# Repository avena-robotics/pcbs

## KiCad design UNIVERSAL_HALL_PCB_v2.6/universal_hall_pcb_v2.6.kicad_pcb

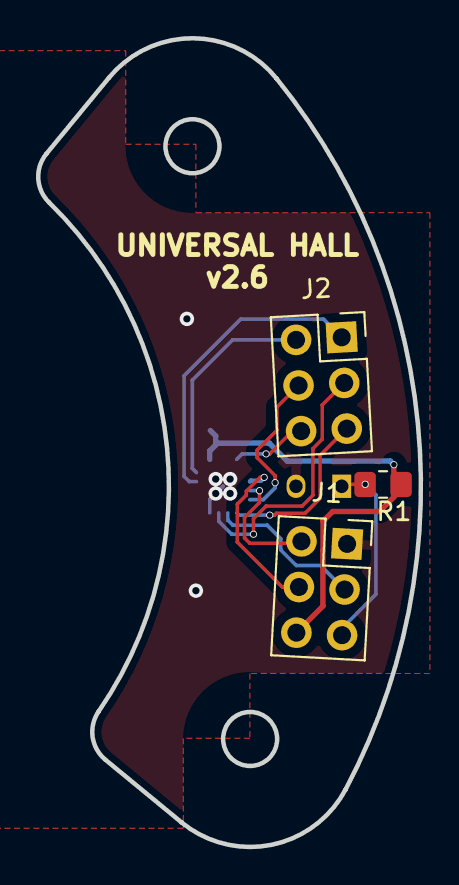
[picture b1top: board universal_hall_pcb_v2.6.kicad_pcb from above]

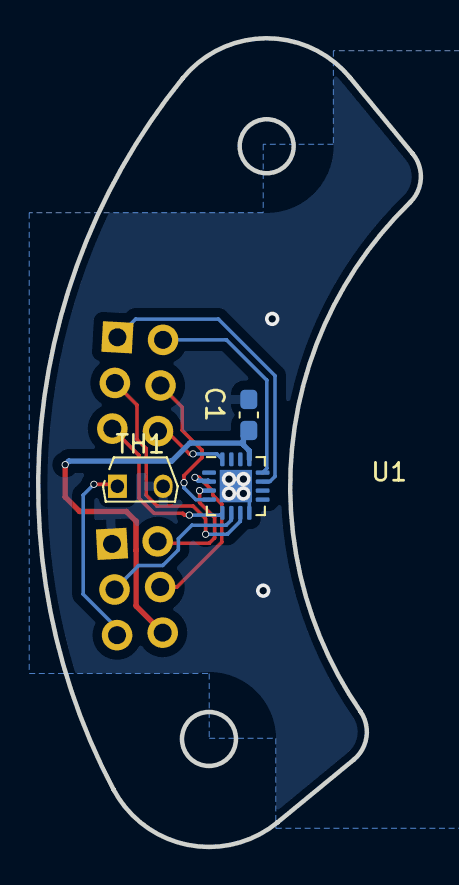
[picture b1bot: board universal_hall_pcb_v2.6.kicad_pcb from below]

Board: 2 copper layers, 21.3 x 44.9 mm, 6 parts (3 on the bottom side), 12 nets.

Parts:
C1: 1uF; C_0603_1608Metric_Pad1.08x0.95mm_HandSolder
J1, J2: Conn_02x03_Odd_Even_MountingPin; PinSocket_2x03_P2.54mm_Vertical
R1: 10k; R_0805_2012Metric_Pad1.20x1.40mm_HandSolder
TH1: Thermistor_PTC; TO-92S-2
U1: MA310; VQFN-16-1EP_3x3mm_P0.5mm_EP1.8x1.8mm

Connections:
+3V3: C1.1, J1.6, R1.1, U1.13 (VDD)
A: J1.4, U1.2 (A)
B: J1.3, U1.6 (B)
CS: J2.5, U1.5 (~CS)
GND: C1.2, J1.1, TH1.2, U1.8 (GND), U1.17 (PAD)
MGH: J2.6, U1.16 (MGH)
MGL: J2.1, U1.11 (MGL)
MISO: J2.3, U1.7 (MISO)
MOSI: J2.4, U1.4 (MOSI)
SCLK: J2.2, U1.12 (SCLK)
VTEMP: J1.5, R1.2, TH1.1
Z: J1.2, U1.3 (Z)

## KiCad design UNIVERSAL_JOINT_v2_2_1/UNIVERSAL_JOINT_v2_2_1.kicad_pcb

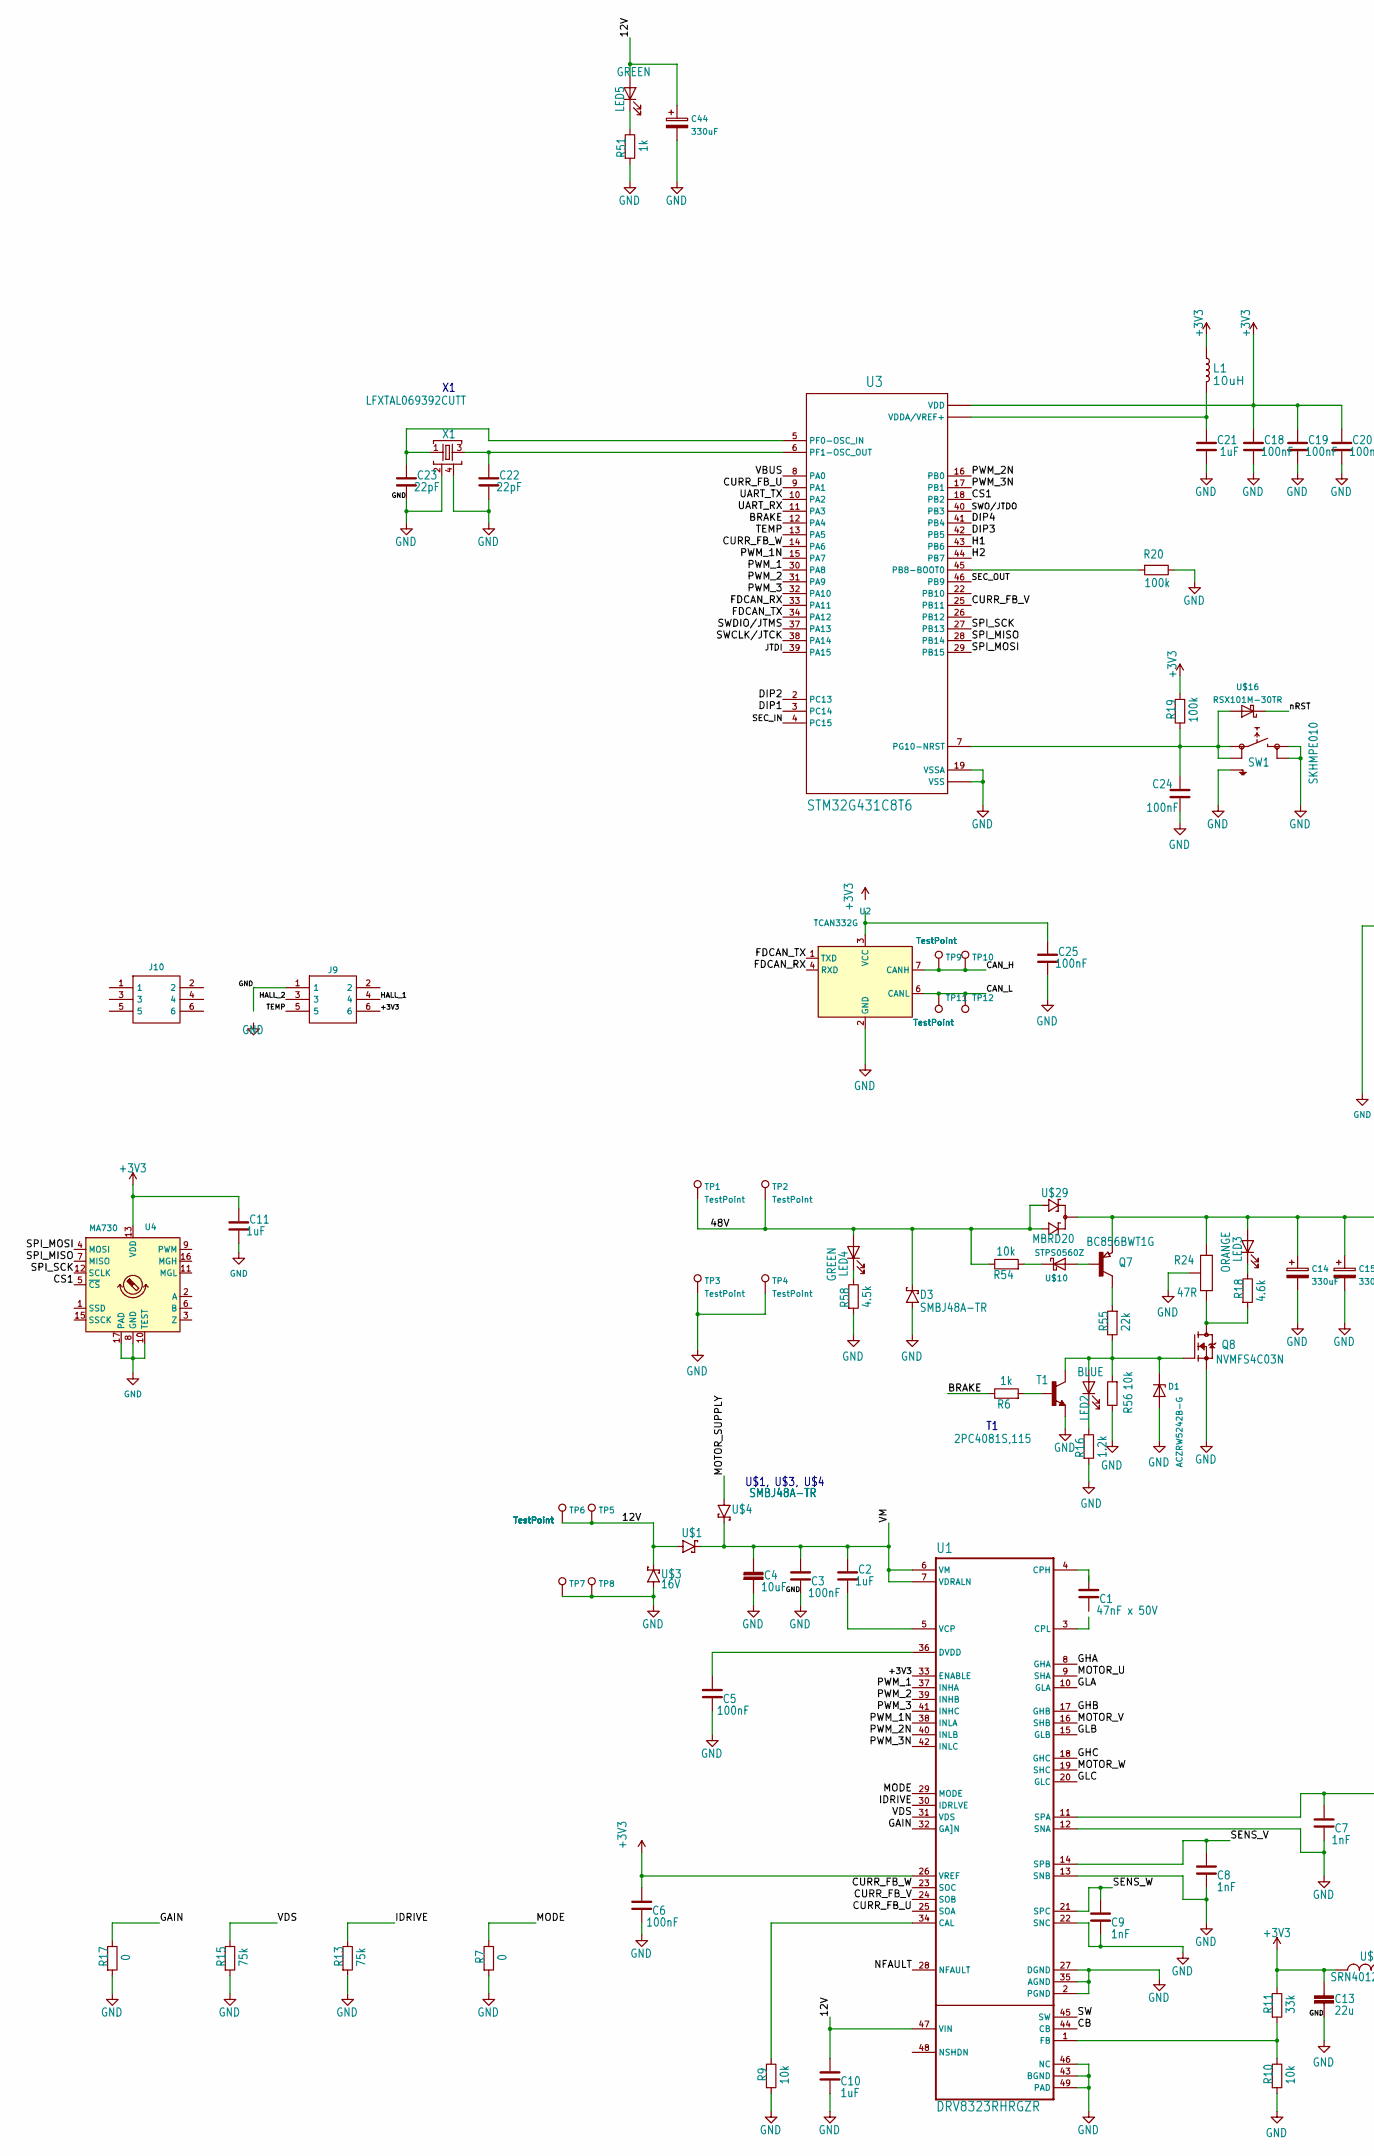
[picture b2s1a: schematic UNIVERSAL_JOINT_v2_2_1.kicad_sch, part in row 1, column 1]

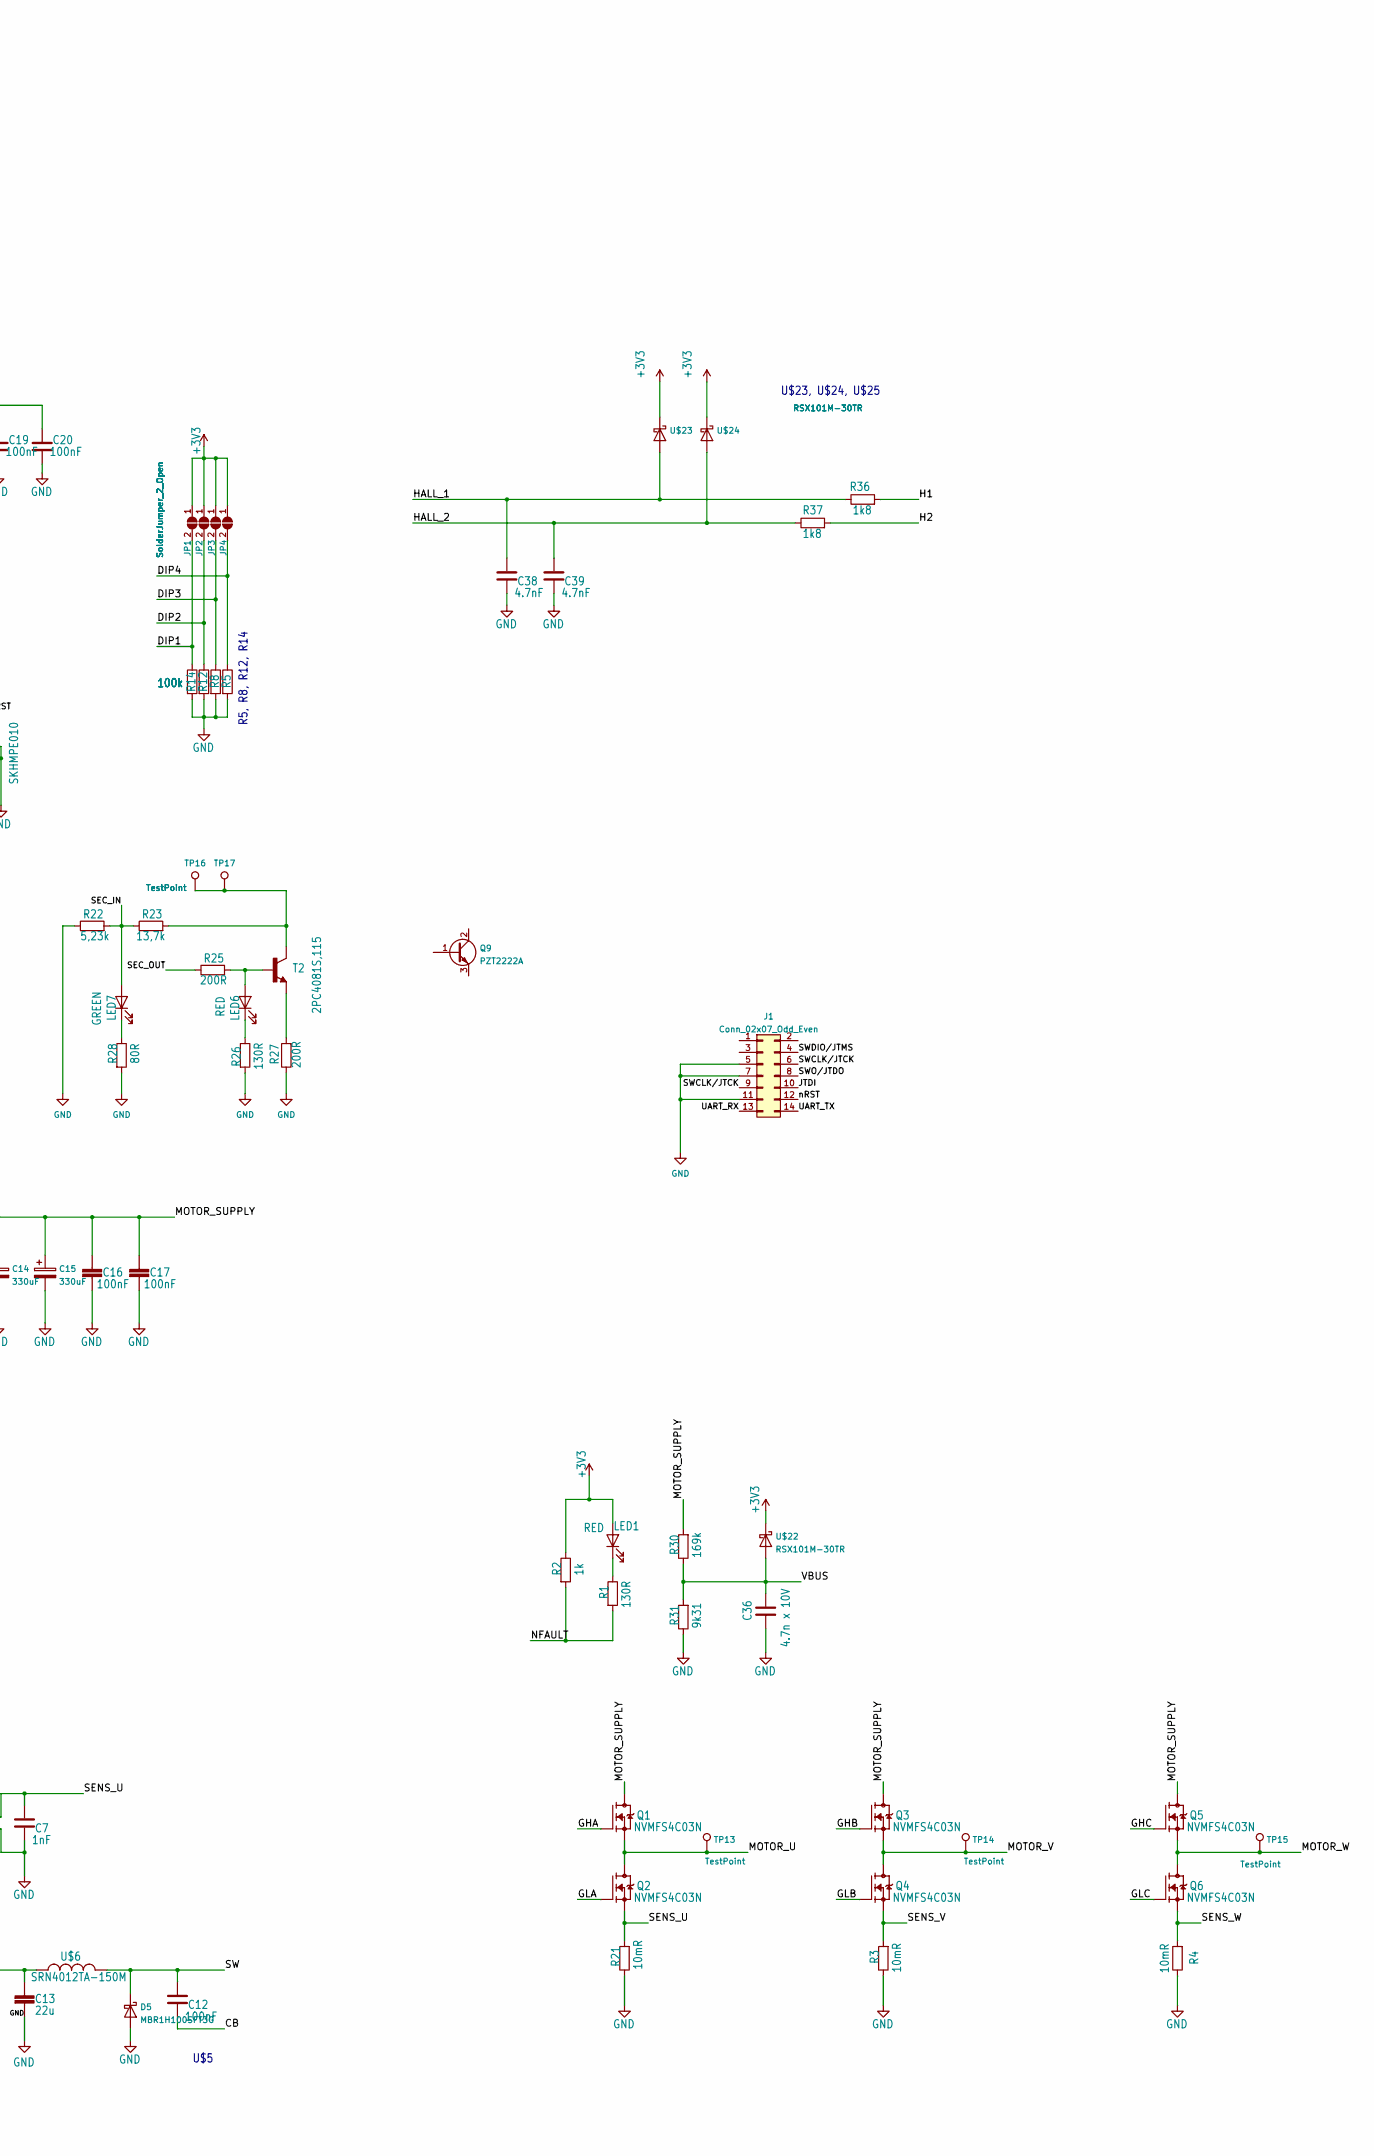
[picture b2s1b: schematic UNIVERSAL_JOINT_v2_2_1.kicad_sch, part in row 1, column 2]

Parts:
C1: 47nF x 50V; C_0603_1608Metric_Pad1.08x0.95mm_HandSolder
C2, C10, C11, C21: 1uF; C_0603_1608Metric_Pad1.08x0.95mm_HandSolder
C3, C5, C6, C12, C18, C19, C20, C24, C25: 100nF; C_0603_1608Metric_Pad1.08x0.95mm_HandSolder
C4: 10uF; C_0805_2012Metric_Pad1.18x1.45mm_HandSolder
C7, C8, C9: 1nF; C_0603_1608Metric_Pad1.08x0.95mm_HandSolder
C13: 22u; C_0805_2012Metric_Pad1.18x1.45mm_HandSolder
C14, C15, C44: 330uF; C_Radial_D12.5mm_H25.0mm_P5.00mm
C16, C17: 100nF; C_0805_2012Metric_Pad1.18x1.45mm_HandSolder
C22, C23: 22pF; C_0603_1608Metric_Pad1.08x0.95mm_HandSolder
C36: 4.7n x 10V; C_0603_1608Metric_Pad1.08x0.95mm_HandSolder
C38, C39: 4.7nF; C_0603_1608Metric_Pad1.08x0.95mm_HandSolder
D1: ACZRW5242B-G; D_SOD-123
D3: SMBJ48A-TR; SMB
D5: MBR1H100SFT3G; D_SOD-123
J1: Conn_02x07_Odd_Even; PinHeader_2x07_P1.27mm_Vertical_SMD
J9, J10: HEADER_MALE_2X3_2.54_SMT; M207810345; Manufacturer_Part_Number M20-7810345; Mouser Part Number 855-M20-7810345
JP1, JP2, JP3, JP4: SolderJumper_2_Open; SolderJumper-2_P1.3mm_Open_TrianglePad1.0x1.5mm
L1: 10uH; 0603
LED1, LED6: RED; D_0603_1608Metric_Pad1.05x0.95mm_HandSolder
LED2: BLUE; D_0603_1608Metric_Pad1.05x0.95mm_HandSolder
LED3: ORANGE; D_0603_1608Metric_Pad1.05x0.95mm_HandSolder
LED4, LED5, LED7: GREEN; D_0603_1608Metric_Pad1.05x0.95mm_HandSolder
Q1, Q2, Q3, Q4, Q5, Q6, Q8: NVMFS4C03N; SO-8FL
Q7: BC856BWT1G; SOT23
Q9: PZT2222A; SOT-223-3_TabPin2
R1, R26: 130R; R_0603_1608Metric_Pad0.98x0.95mm_HandSolder
R2, R6, R51: 1k; R_0603_1608Metric_Pad0.98x0.95mm_HandSolder
R3, R4, R21: 10mR; R_2512_6332Metric_Pad1.40x3.35mm_HandSolder
R5, R8, R12, R14, R19, R20: 100k; R_0603_1608Metric_Pad0.98x0.95mm_HandSolder
R7, R17: 0; R_0603_1608Metric_Pad0.98x0.95mm_HandSolder
R9, R10, R54, R56: 10k; R_0603_1608Metric_Pad0.98x0.95mm_HandSolder
R11: 33k; R_0603_1608Metric_Pad0.98x0.95mm_HandSolder
R13, R15: 75k; R_0603_1608Metric_Pad0.98x0.95mm_HandSolder
R16: 1.2k; R_0603_1608Metric_Pad0.98x0.95mm_HandSolder
R18: 4.6k; R_0603_1608Metric_Pad0.98x0.95mm_HandSolder
R22: 5,23k; R_0603_1608Metric_Pad0.98x0.95mm_HandSolder
R23: 13,7k; R_0603_1608Metric_Pad0.98x0.95mm_HandSolder
R24: 47R; TO-252-2
R25, R27: 200R; R_0603_1608Metric_Pad0.98x0.95mm_HandSolder
R28: 80R; R_0603_1608Metric_Pad0.98x0.95mm_HandSolder
R30: 169k; R_0603_1608Metric_Pad0.98x0.95mm_HandSolder
R31: 9k31; R_0603_1608Metric_Pad0.98x0.95mm_HandSolder
R36, R37: 1k8; R_0603_1608Metric_Pad0.98x0.95mm_HandSolder
R55: 22k; R_0603_1608Metric_Pad0.98x0.95mm_HandSolder
R58: 4.5k; R_0603_1608Metric_Pad0.98x0.95mm_HandSolder
SW1: SKHMPE010; SKHMPXE010
T1, T2: 2PC4081S,115; SOT23-EBC
TP1, TP2, TP3, TP4, TP13, TP14, TP15: TestPoint; Pin_D1.3mm_L11.3mm_W2.8mm_Flat
TP5, TP6, TP7, TP8, TP9, TP10, TP11, TP12, TP16, TP17: TestPoint; Pin_D1.2mm_L11.3mm_W3.0mm_Flat
U1: DRV8323RHRGZR; QFN50P700X700X100-49N
U2: TCAN332G; SOIC-8_3.9x4.9mm_P1.27mm
U3: STM32G431C8T6; LQFP48-7X7
U4: MA730; HVQFN-16-1EP_3x3mm_P0.5mm_EP1.5x1.5mm
U$1, U$4: SMBJ48A-TR; SMB
U$3: 16V; SMB
U$6: SRN4012TA-150M; BEADC4040X120N
U$10: STPS0560Z; D_SOD-123
U$16, U$22, U$23, U$24: RSX101M-30TR; D_SOD-123
U$29: MBRD20; DPACK
X1: LFXTAL069392CUTT; 2.5X2-4-PAD

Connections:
+3V3: C6.1, C11.2, C13.1, C18.2, C19.2, C20.2, J9.6, JP1.1 (A), JP2.1 (A), JP3.1 (A), JP4.1 (A), L1.1, LED1.2 (A), R2.1, R11.1, R19.2, U1.26 (VREF), U1.33 (ENABLE), U3.1 (VDD), U3.24 (VDD), U3.36 (VDD), U3.48 (VDD), U4.13 (VDD), U$6.1, U$22.1 (K), U$23.1 (K), U$24.1 (K)
/12V: C10.1, C44.1, LED5.2 (A), TP5.1, TP6.1, U1.47 (VIN), U$1.A, U$3.C
/48V: D3.C, LED4.2 (A), R54.1, TP1.1, TP2.1, U$29.1 (A1), U$29.3 (A2)
/BRAKE: R6.1, U3.12 (PA4)
/CAN_H: TP9.1, TP10.1, U2.7 (CANH)
/CAN_L: TP11.1, TP12.1, U2.6 (CANL)
/CB: C12.2, U1.44 (CB)
/CS1: U3.18 (PB2), U4.5 (~CS)
/CURR_FB_U: U1.25 (SOA), U3.9 (PA1)
/CURR_FB_V: U1.24 (SOB), U3.25 (PB11)
/CURR_FB_W: U1.23 (SOC), U3.14 (PA6)
/DIP1: JP1.2 (B), R14.1, U3.3 (PC14)
/DIP2: JP2.2 (B), R12.1, U3.2 (PC13)
/DIP3: JP3.2 (B), R8.1, U3.42 (PB5)
/DIP4: JP4.2 (B), R5.1, U3.41 (PB4)
/FDCAN_RX: U2.4 (RXD), U3.33 (PA11)
/FDCAN_TX: U2.1 (TXD), U3.34 (PA12)
/GAIN: R17.1, U1.32 (GA]N)
/GHA: Q1.P$4 (G), U1.8 (GHA)
/GHB: Q3.P$4 (G), U1.17 (GHB)
/GHC: Q5.P$4 (G), U1.18 (GHC)
/GLA: Q2.P$4 (G), U1.10 (GLA)
/GLB: Q4.P$4 (G), U1.15 (GLB)
/GLC: Q6.P$4 (G), U1.20 (GLC)
/H1: R36.2, U3.43 (PB6)
/H2: R37.2, U3.44 (PB7)
/HALL_1: C38.1, J9.4, R36.1, U$23.2 (A)
/HALL_2: C39.1, J9.3, R37.1, U$24.2 (A)
/IDRIVE: R13.1, U1.30 (IDRLVE)
/JTDI: J1.10, U3.39 (PA15)
/MODE: R7.1, U1.29 (MODE)
/MOTOR_SUPPLY: C14.1, C15.1, C16.1, C17.1, LED3.2 (A), Q1.P$5 (D), Q3.P$5 (D), Q5.P$5 (D), Q7.2 (E), R24.3, R30.2, U$4.A, U$29.2 (C)
/MOTOR_U: Q1.P$1 (S), Q1.P$2 (S), Q1.P$3 (S), Q2.P$5 (D), TP13.1, U1.9 (SHA)
/MOTOR_V: Q3.P$1 (S), Q3.P$2 (S), Q3.P$3 (S), Q4.P$5 (D), TP14.1, U1.16 (SHB)
/MOTOR_W: Q5.P$1 (S), Q5.P$2 (S), Q5.P$3 (S), Q6.P$5 (D), TP15.1, U1.19 (SHC)
/NFAULT: R1.2, R2.2, U1.28 (NFAULT)
/PWM_1: U1.37 (INHA), U3.30 (PA8)
/PWM_1N: U1.38 (INLA), U3.15 (PA7)
/PWM_2: U1.39 (INHB), U3.31 (PA9)
/PWM_2N: U1.40 (INLB), U3.16 (PB0)
/PWM_3: U1.41 (INHC), U3.32 (PA10)
/PWM_3N: U1.42 (INLC), U3.17 (PB1)
/SEC_IN: LED7.2 (A), R22.2, R23.1, U3.4 (PC15)
/SEC_OUT: R25.1, U3.46 (PB9)
/SENS_U: C7.1, Q2.P$1 (S), Q2.P$2 (S), Q2.P$3 (S), R21.2, U1.11 (SPA)
/SENS_V: C8.1, Q4.P$1 (S), Q4.P$2 (S), Q4.P$3 (S), R3.2, U1.14 (SPB)
/SENS_W: C9.1, Q6.P$1 (S), Q6.P$2 (S), Q6.P$3 (S), R4.2, U1.21 (SPC)
/SPI_MISO: U3.28 (PB14), U4.7 (MISO)
/SPI_MOSI: U3.29 (PB15), U4.4 (MOSI)
/SPI_SCK: U3.27 (PB13), U4.12 (SCLK)
/SW: C12.1, D5.1 (K), U1.45 (SW), U$6.2
/SWCLK/JTCK: J1.6, J1.9, U3.38 (PA14)
/SWDIO/JTMS: J1.4, U3.37 (PA13)
/SWO/JTDO: J1.8, U3.40 (PB3)
/TEMP: J9.5, U3.13 (PA5)
/UART_RX: J1.13, U3.11 (PA3)
/UART_TX: J1.14, U3.10 (PA2)
/VBUS: C36.2, R30.1, R31.2, U3.8 (PA0), U$22.2 (A)
/VDS: R15.1, U1.31 (VDS)
/VM: C2.2, C3.1, C4.1, U1.6 (VM), U1.7 (VDRALN), U$1.C, U$4.C
/nRST: J1.12, U$16.1 (K)
GND: C3.2, C4.2, C5.2, C6.2, C7.2, C8.2, C9.2, C10.2, C11.1, C13.2, C14.2, C15.2, C16.2, C17.2, C18.1, C19.1, C20.1, C21.1, C22.1, C23.1, C24.1, C25.1, C36.1, C38.2, C39.2, C44.2, D1.2 (A), D3.A, D5.2 (A), J1.5, J1.7, J1.11, J9.1, Q8.P$1 (S), Q8.P$2 (S), Q8.P$3 (S), R3.1, R4.1, R5.2, R7.2, R8.2, R9.2, R10.2, R12.2, R13.2, R14.2, R15.2, R16.2, R17.2, R20.1, R21.1, R22.1, R24.2, R26.2, R27.1, R28.2, R31.1, R51.2, R56.1, R58.2, SW1.3 (2.1), SW1.4 (2.2), SW1.5 (SH), T1.E, TP3.1, TP4.1, TP7.1, TP8.1, U1.2 (PGND), U1.12 (SNA), U1.13 (SNB), U1.22 (SNC), U1.27 (DGND), U1.35 (AGND), U1.43 (BGND), U1.46 (NC), U1.49 (PAD), U2.2 (GND), U3.19 (VSSA), U3.23 (VSS), U3.35 (VSS), U3.47 (VSS), U4.8 (GND), U4.10 (TEST), U4.17 (PAD), U$3.A, X1.2, X1.4
unnamed: C24.2, R19.1, SW1.1 (1.1), SW1.2 (1.2), U3.7 (PG10-NRST), U$16.2 (A)
unnamed: C25.2, U2.3 (VCC)
unnamed: D1.1 (K), LED2.2 (A), Q8.P$4 (G), R55.1, R56.2, T1.C
unnamed: C21.2, L1.2, U3.20 (VDDA/VREF+), U3.21 (VDDA/VREF+)
unnamed: LED1.1 (K), R1.1
unnamed: LED2.1 (K), R16.1
unnamed: LED3.1 (K), R18.1
unnamed: LED4.1 (K), R58.1
unnamed: LED6.1 (K), R26.1
unnamed: LED6.2 (A), R25.2, T2.B
unnamed: LED7.1 (K), R28.1
unnamed: Q7.1 (B), U$10.2 (A)
unnamed: Q7.3 (C), R55.2
unnamed: Q8.P$5 (D), R18.2, R24.1
unnamed: LED5.1 (K), R51.1
unnamed: R6.2, T1.B
unnamed: R23.2, T2.C, TP16.1, TP17.1
unnamed: R27.2, T2.E
unnamed: R10.1, R11.2, U1.1 (FB)
unnamed: C2.1, U1.5 (VCP)
unnamed: R9.1, U1.34 (CAL)
unnamed: C5.1, U1.36 (DVDD)
unnamed: C23.2, U3.5 (PF0-OSC_IN), X1.1
unnamed: C22.2, U3.6 (PF1-OSC_OUT), X1.3
unnamed: R20.2, U3.45 (PB8-BOOT0)
unnamed: R54.2, U$10.1 (K)

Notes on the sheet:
U$1, U$3, U$4
U$5
R5, R8, R12, R14
U$23, U$24, U$25

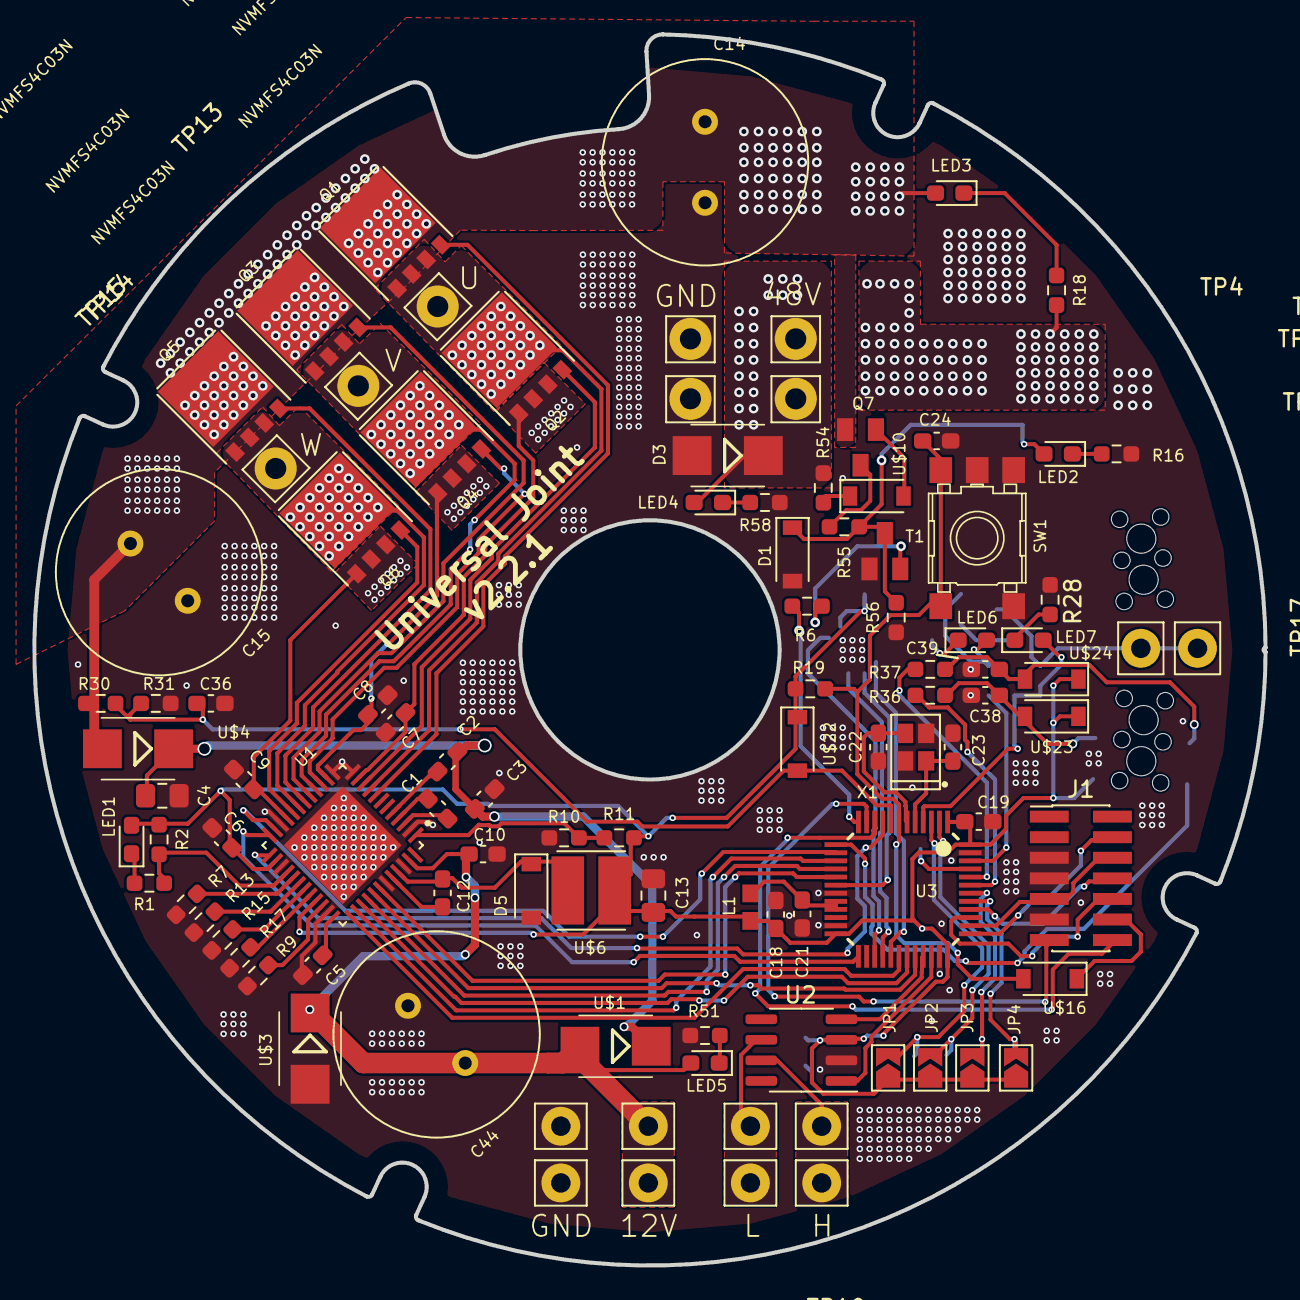
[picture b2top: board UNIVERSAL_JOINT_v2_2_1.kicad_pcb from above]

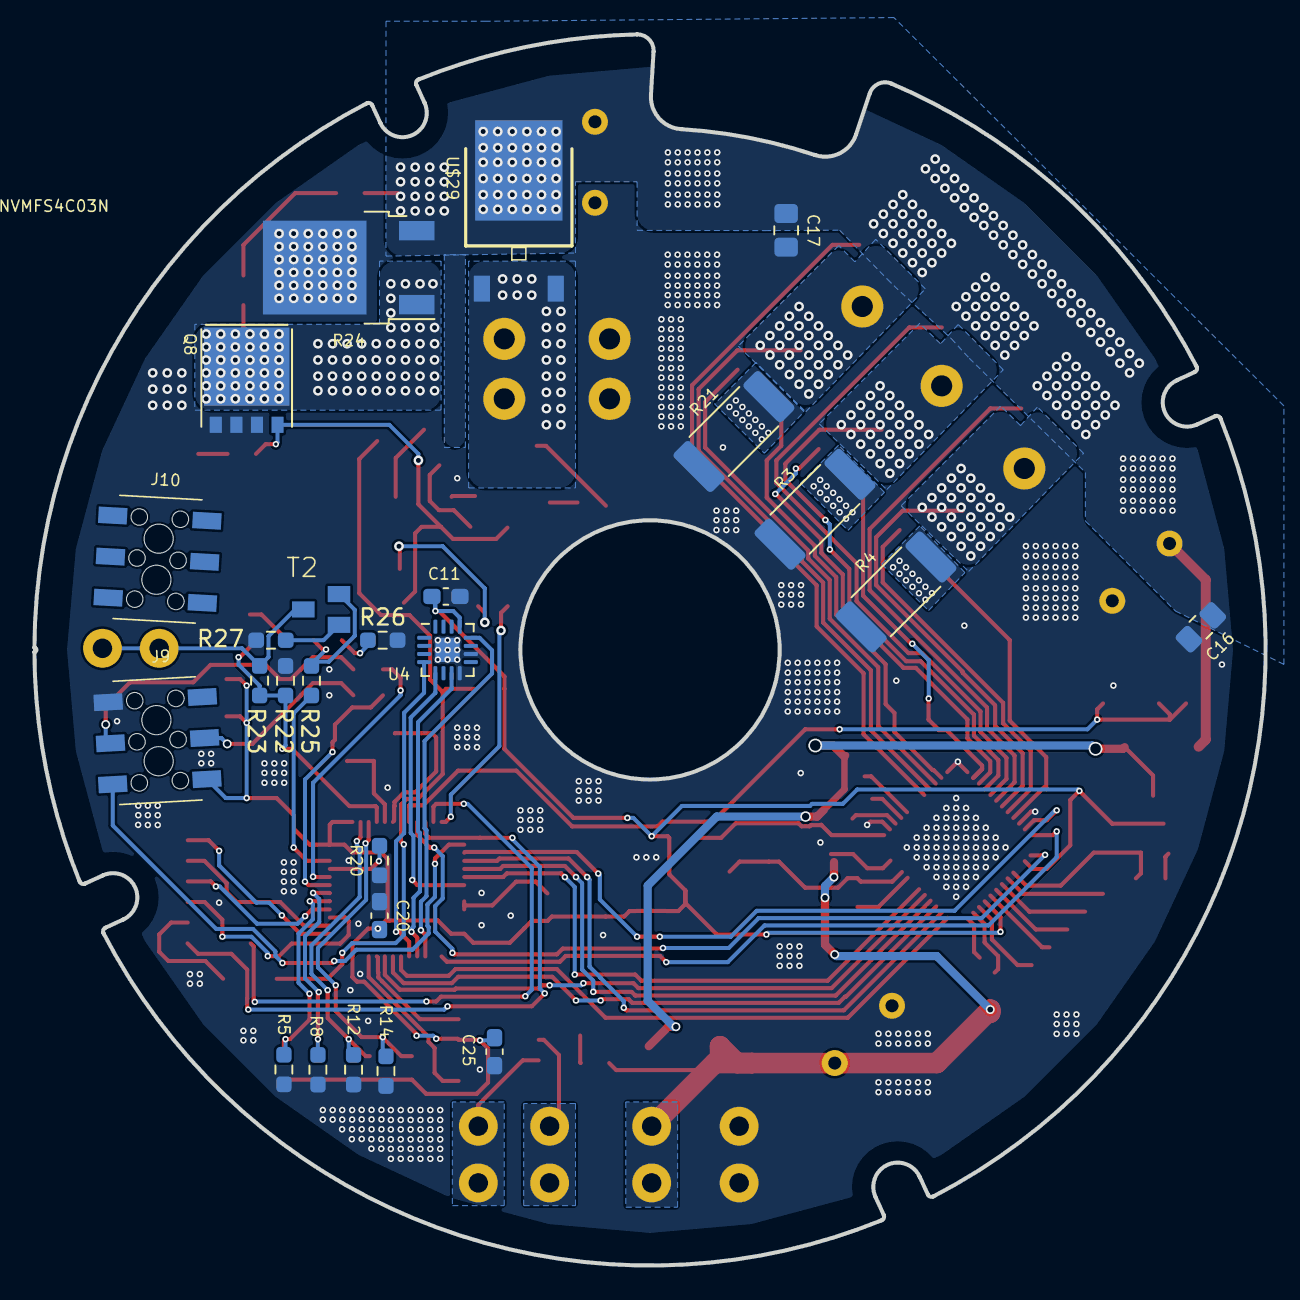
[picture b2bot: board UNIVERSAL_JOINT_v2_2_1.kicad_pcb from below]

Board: 2 copper layers, 76.0 x 76.0 mm, 127 parts (25 on the bottom side), 88 nets.

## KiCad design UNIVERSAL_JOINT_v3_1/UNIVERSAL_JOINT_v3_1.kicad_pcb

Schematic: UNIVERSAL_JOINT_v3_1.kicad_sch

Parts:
C1: 10uF 25v; C_0603_1608Metric_Pad1.08x0.95mm_HandSolder
C2, C13, C14, C15: 220nF 100V; C_0603_1608Metric_Pad1.08x0.95mm_HandSolder
C4, C5: 6.8pF; C_0603_1608Metric_Pad1.08x0.95mm_HandSolder
C6: 10uF; C_0603_1608Metric_Pad1.08x0.95mm_HandSolder
C7, C9, C11, C12, C40: 100nF; C_0603_1608Metric_Pad1.08x0.95mm_HandSolder
C8, C10, C201: 1uF; C_0603_1608Metric_Pad1.08x0.95mm_HandSolder
C16, C17, C18: 1uF 25V; C_0603_1608Metric_Pad1.08x0.95mm_HandSolder
C19: 33nF; C_0603_1608Metric_Pad1.08x0.95mm_HandSolder
C25, C26, C27: 82nF 5%; C_0603_1608Metric_Pad1.08x0.95mm_HandSolder
C31, C32: 330uF 100V; CP_Radial_D12.5mm_P5.00mm
C41: 100 nF; C_0603_1608Metric_Pad1.08x0.95mm_HandSolder
C202: 220uF 100V; CP_Radial_D6.3mm_P2.50mm
D1: STPS1H100A; D_0603_1608Metric_Pad1.05x0.95mm_HandSolder
D2, D3, D4, D5, D6, D7: BAT48, 40 V; D_0603_1608Metric_Pad1.05x0.95mm_HandSolder
D8, D9, D10, D11: BAT30K; D_0603_1608Metric_Pad1.05x0.95mm_HandSolder
D201: GREEN; D_0603_1608Metric_Pad1.05x0.95mm_HandSolder
D202: SMBJ48A-TR; D_0603_1608Metric_Pad1.05x0.95mm_HandSolder
D203: BRIDGED; DPACK
D204, D205: NM; D_SOD-123
D206, D207, D208: NM; D_0603_1608Metric_Pad1.05x0.95mm_HandSolder
J9: HEADER_MALE_2X3_2.54_SMT; M207810345; Manufacturer_Part_Number M20-7810345; Mouser Part Number 855-M20-7810345
J10: N.M.; M207810345; Manufacturer_Part_Number M20-7810345; Mouser Part Number 855-M20-7810345
J12: FTSH-107-01-L-DV-K-TR; SAMTEC_FTSH-107-01-L-DV-K-TR; PARTREV R
JP1, JP2, JP3, JP4: SolderJumper_2_Open; SolderJumper-2_P1.3mm_Open_TrianglePad1.0x1.5mm
L1: 18uH, 1A; L_Wuerth_WE-PD2-Typ-MS
NT1: NetTie_2; NetTie-2_SMD_Pad0.5mm
Q1, Q2, Q3, Q4, Q5, Q6: IAUC120N06S5L; STL110N10F7
Q201: NM; SOT23
Q202: NM; STL110N10F7
Q203: 2PC4081S,115; SOT23-EBC
R1: n.m; R_0603_1608Metric_Pad0.98x0.95mm_HandSolder
R6, R7, R8, R9, R19, R20, R21: 0; R_0603_1608Metric_Pad0.98x0.95mm_HandSolder
R13, R14, R15, R25, R26, R27: 33; R_0603_1608Metric_Pad0.98x0.95mm_HandSolder
R31, R32, R33, R34, R35, R36: 10m 1% 3W; R_2512_6332Metric_Pad1.40x3.35mm_HandSolder
R37: 72.3k 1%; R_0603_1608Metric_Pad0.98x0.95mm_HandSolder
R39: 3.01k 1%; R_0603_1608Metric_Pad0.98x0.95mm_HandSolder
R41, R42, R43, R47, R48, R49: 22k 1%; R_0603_1608Metric_Pad0.98x0.95mm_HandSolder
R44, R45, R46, R50, R51, R52: 1.5k 1%; R_0603_1608Metric_Pad0.98x0.95mm_HandSolder
R53, R54, R55: 11k 1%; R_0603_1608Metric_Pad0.98x0.95mm_HandSolder
R56, R58, R60: 68k 1%; R_0603_1608Metric_Pad0.98x0.95mm_HandSolder
R57, R59, R61: 27k 1%; R_0603_1608Metric_Pad0.98x0.95mm_HandSolder
R62, R63, R64: 3.9k 1%; R_0603_1608Metric_Pad0.98x0.95mm_HandSolder
R90, R213, R214, R215, R216: 100k; R_0603_1608Metric_Pad0.98x0.95mm_HandSolder
R92: 200; R_0603_1608Metric_Pad0.98x0.95mm_HandSolder
R201: 4.5k; R_0603_1608Metric_Pad0.98x0.95mm_HandSolder
R202, R203, R204, R209, R211, R212: NM; R_0603_1608Metric_Pad0.98x0.95mm_HandSolder
R205: NM; DPACK
R206: 5,23k; R_0603_1608Metric_Pad0.98x0.95mm_HandSolder
R207: 13,7k; R_0603_1608Metric_Pad0.98x0.95mm_HandSolder
R208, R210: 200R; R_0603_1608Metric_Pad0.98x0.95mm_HandSolder
SW3: SKHUALE010
TP1, TP2: 48V; 1-726388-2
TP3, TP4: GND; 1-726388-2
TP5, TP6: 12V; 61-2348-11_0030
TP7, TP8: CANL; 61-2348-11_0030
TP9, TP10: CANH; 61-2348-11_0030
TP11, TP12, TP13: 1-726388-2
TP14, TP15: TestPoint; 61-2348-11_0030
TP16, TP17: GND; 61-2348-11_0030
TP18, TP19, TP20, TP21, TP22, TP23: TestPoint_Small; TestPoint_Pad_1.0x1.0mm
U1: STSPIN32G4
U2: TCAN332G; SO-8_3.9x4.9mm_P1.27mm
U6: MA730; HVQFN-16-1EP_3x3mm_P0.5mm_EP1.5x1.5mm
X1: ECS-240-8-36B2-CKM-TR; Crystal_SMD_2520-4Pin_2.5x2.0mm

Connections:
/48V: D201.2 (A), D202.1 (K), D203.1 (A1), D203.3 (A2), R202.2, TP1.1, TP2.1
/A: J9.4, U1.57 (PB6)
/B: J9.3, U1.58 (PB7)
/BEARING_TEMP: J9.2, U1.17 (PA4)
/BOOT1: C16.2, U1.41 (BOOT1)
/BOOT2: C17.2, U1.38 (BOOT2)
/BOOT3: C18.2, U1.35 (BOOT3)
/CAN_RX: U1.47 (PA11), U2.4 (RXD)
/CAN_TX: U1.48 (PA12), U2.1 (TXD)
/DIP1: JP1.1 (A), R213.2, U1.44 (PA8)
/DIP2: JP2.1 (A), R214.2, U1.60 (PB9)
/DIP3: JP3.1 (A), R215.2, U1.59 (PB8)
/DIP4: JP4.1 (A), R216.2, U1.53 (PD2)
/GHS1: D2.1 (K), R13.1, U1.43 (GHS1)
/GHS1_MOS: D2.2 (A), Q1.4, R13.2
/GHS2: D3.1 (K), R14.1, U1.40 (GHS2)
/GHS2_MOS: D3.2 (A), Q2.4, R14.2
/GHS3: D4.1 (K), R15.1, U1.37 (GHS3)
/GHS3_MOS: D4.2 (A), Q3.4, R15.2
/GLS1: D5.1 (K), R25.1, U1.29 (GLS1)
/GLS1_MOS: D5.2 (A), Q4.4, R25.2
/GLS2: D6.1 (K), R26.1, U1.30 (GLS2)
/GLS2_MOS: D6.2 (A), Q5.4, R26.2
/GLS3: D7.1 (K), R27.1, U1.31 (GLS3)
/GLS3_MOS: D7.2 (A), Q6.4, R27.2
/JTDI: J12.10, U1.51 (PA15)
/MA710_CS: J10.5, U1.3 (PC13)
/MA730_CS: U1.12 (PC3), U6.5 (~CS)
/MGH: J10.6
/MGL: J10.1
/MOTOR_TEMP: J9.5, U1.21 (PC4)
/OPN1: R50.2, R53.1, U1.16 (PA3)
/OPN2: R51.2, R54.1, U1.22 (PC5)
/OPN3: R52.2, R55.1, U1.25 (PB2)
/OPO1: R53.2, U1.15 (PA2)
/OPO2: R54.2, U1.19 (PA6)
/OPO3: R55.2, U1.24 (PB1)
/OPP1: R41.1, R44.2, R47.2, U1.14 (PA1)
/OPP2: R42.1, R45.2, R48.2, U1.20 (PA7)
/OPP3: R43.1, R46.2, R49.2, U1.23 (PB0)
/OSC_IN: C4.2, U1.6 (PF0), X1.1
/OSC_OUT: C5.2, U1.7 (PF1), X1.3
/OUT1: C16.1, R19.1, U1.42 (OUT1)
/OUT2: C17.1, R20.1, U1.39 (OUT2)
/OUT3: C18.1, R21.1, U1.36 (OUT3)
/SEC_IN: D208.2 (A), R206.2, R207.1, U1.4 (PC14)
/SEC_OUT: R208.1, U1.5 (PC15)
/SPI_MISO: J10.3, TP21.1, U1.55 (PB4), U6.7 (MISO)
/SPI_MOSI: J10.4, TP23.1, U1.56 (PB5), U6.4 (MOSI)
/SPI_SCK: J10.2, TP22.1, U1.18 (PA5), U6.12 (SCLK)
/SW: D1.1 (K), L1.1, U1.62 (SW)
/SWCLK/JTCK: J12.06, J12.09, U1.50 (PA14)
/SWDIO/JTMS: J12.04, U1.49 (PA13)
/SWO/JTDO: J12.08, U1.54 (PB3)
/TORQUE_CS: TP20.1, U1.28 (PB10)
/U: Q1.1, Q1.2, Q1.3, Q4.5, Q4.6, Q4.7, Q4.8, R19.2, R56.1, TP11.1
/UART_RX: J12.13, U1.46 (PA10)
/UART_TX: J12.14, U1.45 (PA9)
/V: Q2.1, Q2.2, Q2.3, Q5.5, Q5.6, Q5.7, Q5.8, R20.2, R58.1, TP12.1
/VBAT: C12.2, R7.2, U1.2 (VBAT)
/VBUS: C19.2, D8.2 (A), R37.1, R39.2, U1.13 (PA0)
/VCC: C1.2, C202.1, L1.2, R6.1, TP5.1, TP6.1, U1.63 (VCC)
/VDD: C6.2, C7.2, C41.1, C201.2, J9.6, R7.1, R8.1, R90.2, R213.1, R214.1, R215.1, R216.1, TP19.1, U1.1 (REG3V3/VDD), U2.3 (VCC), U6.13 (VDD)
/VDDA: C8.2, C9.2, D8.1 (K), D9.1 (K), D10.1 (K), D11.1 (K), R8.2, R9.1, U1.27 (VDDA)
/VOUT1: C25.1, D9.2 (A), R57.2, R62.2, U1.9 (PC0)
/VOUT2: C26.1, D10.2 (A), R59.2, R63.2, U1.10 (PC1)
/VOUT3: C27.1, D11.2 (A), R61.2, R64.2, U1.11 (PC2)
/VREF+: C10.2, C11.2, R9.2, R41.2, R42.2, R43.2, U1.26 (VREF+)
/VREGIN: R6.2, U1.64 (REGIN)
/VSHUNT1P: Q4.1, Q4.2, Q4.3, R31.1, R32.1, R44.1
/VSHUNT2P: Q5.1, Q5.2, Q5.3, R33.1, R34.1, R45.1
/VSHUNT3P: Q6.1, Q6.2, Q6.3, R35.1, R36.1, R46.1
/W: Q3.1, Q3.2, Q3.3, Q6.5, Q6.6, Q6.7, Q6.8, R21.2, R60.1, TP13.1
/nRST: J12.12, R92.1, U1.8 (PG10)
GND: C1.1, C2.1, C4.1, C5.1, C6.1, C7.1, C8.1, C9.1, C10.1, C11.1, C12.1, C19.1, C25.2, C26.2, C27.2, C40.1, C41.2, C201.1, C202.2, D1.2 (A), J9.1, J12.05, J12.07, J12.11, JP1.2 (B), JP2.2 (B), JP3.2 (B), JP4.2 (B), NT1.1, R39.1, R47.1, R48.1, R49.1, R62.1, R63.1, R64.1, R206.1, R209.2, R210.1, R212.2, SW3.1, SW3.2, TP16.1, TP17.1, TP18.1, U1.32 (PGND), U1.65 (VSS), U2.2 (GND), U6.8 (GND), U6.10 (TEST), U6.17 (PAD), X1.2, X1.4
GNDPWR: C13.1, C14.1, C15.1, C31.2, C32.2, D202.2 (A), D205.2 (A), NT1.2, Q202.1, Q202.2, Q202.3, R31.2, R32.2, R33.2, R34.2, R35.2, R36.2, R50.1, R51.1, R52.1, R201.1, R204.1, R205.2, TP3.1, TP4.1
unnamed: C40.2, R90.1, R92.2, SW3.3 (K), SW3.4 (A)
unnamed: D201.1 (K), R201.2
unnamed: D204.1 (K), R202.1
unnamed: D204.2 (A), Q201.1 (B)
unnamed: D205.1 (K), Q202.4, R203.1, R204.2
unnamed: D206.1 (K), R209.1
unnamed: D206.2 (A), Q203.B, R208.2
unnamed: D207.1 (K), R211.1
unnamed: D208.1 (K), R212.1
unnamed: Q201.3 (C), R203.2
unnamed: Q202.5, Q202.6, Q202.7, Q202.8, R205.1, R211.2
unnamed: Q203.C, R207.2, TP14.1, TP15.1
unnamed: Q203.E, R210.2
unnamed: R1.1, U1.61 (VM)
unnamed: R56.2, R57.1
unnamed: R58.2, R59.1
unnamed: R60.2, R61.1
unnamed: TP7.1, TP8.1, U2.6 (CANL)
unnamed: TP9.1, TP10.1, U2.7 (CANH)
VM: C2.2, C13.2, C14.2, C15.2, C31.1, C32.1, D203.2 (C), D207.2 (A), Q1.5, Q1.6, Q1.7, Q1.8, Q2.5, Q2.6, Q2.7, Q2.8, Q3.5, Q3.6, Q3.7, Q3.8, Q201.2 (E), R1.2, R37.2, R205.3

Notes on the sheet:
VM - 48V VCC - Gate driving supply voltage - 12V VREGIN - 3.3 V LDO linear regulator input - 12V VDD - 3,3V VBAT VDDA VREF+ - 3,3V do dzielnika napiecia GND
ZAMIENIĆ NA NETTIE
ZAMIENIĆ NA DRABINKĘ LUB WYWALIĆ
MOŻNA ZWOLNIĆ
R5, R8, R12, R14
C2 przed rezystorem
DODAĆ LED ZASILANIA 12V
R201 ZAMIENIĆ NA 2 SZTUKI RES SMD 4.7K OHM 5% 1/2W 0805
NOT MOUNTED
CONNECTORS
WBUDOWANY OPAMP
A,B DODAĆ RC FILTER 1k 10pF
DODAĆ FILTR RC DO AB
PRZY SCREF DODAĆ DZIELNIK - BRAK!

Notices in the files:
parts and their libraries:
Copyright 2021 Accelerated Designs. All rights reserved.
